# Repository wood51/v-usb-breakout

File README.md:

v-usb-breakout
==============

V-Usub breakout board : connecteur + adaptation des signaux

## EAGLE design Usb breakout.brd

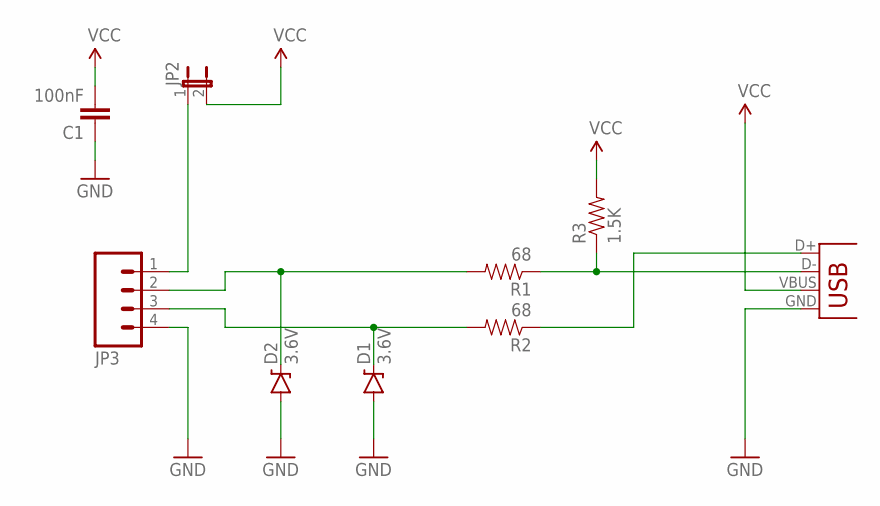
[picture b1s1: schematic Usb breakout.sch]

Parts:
C1: 100nF; CAP-PTH-SMALLEZ
D1, D2: 3.6V; DIODE-ZENER
JP1: USB-B; USB-B-PTH
JP2: JUMPER-2-OLDPTH; 1X02
JP3: M04PTH; 1X04
R1, R2: 68; AXIAL-0.4
R3: 1.5K; AXIAL-0.4

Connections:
GND: C1.1, D1.P$2 (A), D2.P$2 (A), JP1.GND, JP3.4
unnamed: JP1.D-, R1.P$1 (1), R3.P$1 (1)
unnamed: D2.P$1 (C), JP3.2, R1.P$2 (2)
unnamed: D1.P$1 (C), JP3.3, R2.P$2 (2)
unnamed: JP1.D+, R2.P$1 (1)
unnamed: JP2.1, JP3.1
VCC: C1.2, JP1.VBUS, JP2.2, R3.P$2 (2)

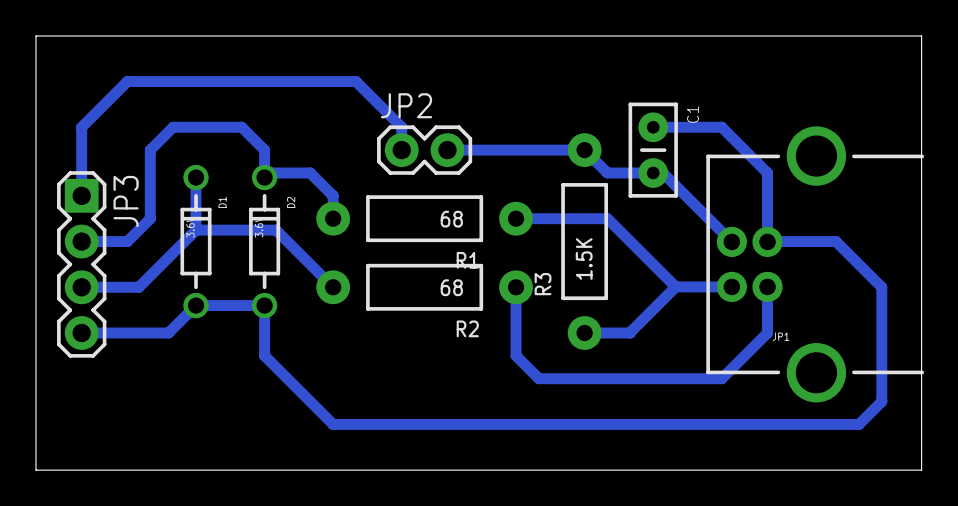
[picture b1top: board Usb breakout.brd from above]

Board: 2 copper layers, 49.2 x 24.1 mm, 9 parts (0 on the bottom side), 7 nets.

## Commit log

2014-08-04 Ajout du schémas et du PCB

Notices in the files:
parts and their libraries:
SparkFun-Connectors: Licensing: Creative Commons ShareAlike 4.0 International - https://creativecommons.org/licenses/by-sa/4.0
